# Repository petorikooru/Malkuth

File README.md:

# Malkuth

Idk, the name just comes up in my head (that malkuth from BA)

> [!CAUTION]
> For now, DO NOT USE the PCB Design unless you know what you are doing.
> There are quite silly (and tiny bit major) design flaws on there

> [!NOTE]  
> For now, the audio handling is a bit stuttery on some FLAC audio
> (especially on 24 bit one). I will make it a todo list for now

Basically it is a rewrite version of the previous project of mine [uta](https://github.com/petorikooru/uta)

I create this to fulfill my final project of Microcomputer class lmao.

## Dependencies

- TFT_eSPI + FT6236 + PNGdec
- arduino-audio-tools + libfoxenflac + libmp3helix + libaac + libwav
- SdFat

## Hardware Components

- ILI9488 Capacitive Touch Screen Display
- PCM5102a DAC
- MicroSD Card Module
- ESP32-S3 N16R8
- Kailh Choc v2 switch
- Other small components stuff

For now, 16 MB Storage size is needed to keep the font files (they take like 50% of the spaces 💀). I will make them .vlw files and store it inside SPIFFS or LittleFS (that is the task of future me though)

## Screenshot

<table>
  <tr>
    <td> </td>
    <td> </td>
    <td> </td>
  </tr> 
</table>

## TODO List

- Make the audio a task itself just like Display (The main trouble is that SdFat is not really thread safe)
- Actually handle audio cover image (jpg and png)
- More performance fixing stuff
- ~Actually handle UI correctly instead of reloading from scratch~ (Kinda done?)
- 3D Printable Case

## Far (not really) to the future TODO LIST

- Maybe split the processing to different chip so that the Display will be driven by RP2040 and the Audio (and perhaps even bluetooth functionality) will be driven by ESP32-S3 (or more powerful counterpart)
- Fix the PCB Design and implement actual charging functionality
- Add speaker (maybe will salvage from iphone speaker or something) and implement automatic audio switching
- RTC clock?
- Animation (i dont think it is powerful enough though)

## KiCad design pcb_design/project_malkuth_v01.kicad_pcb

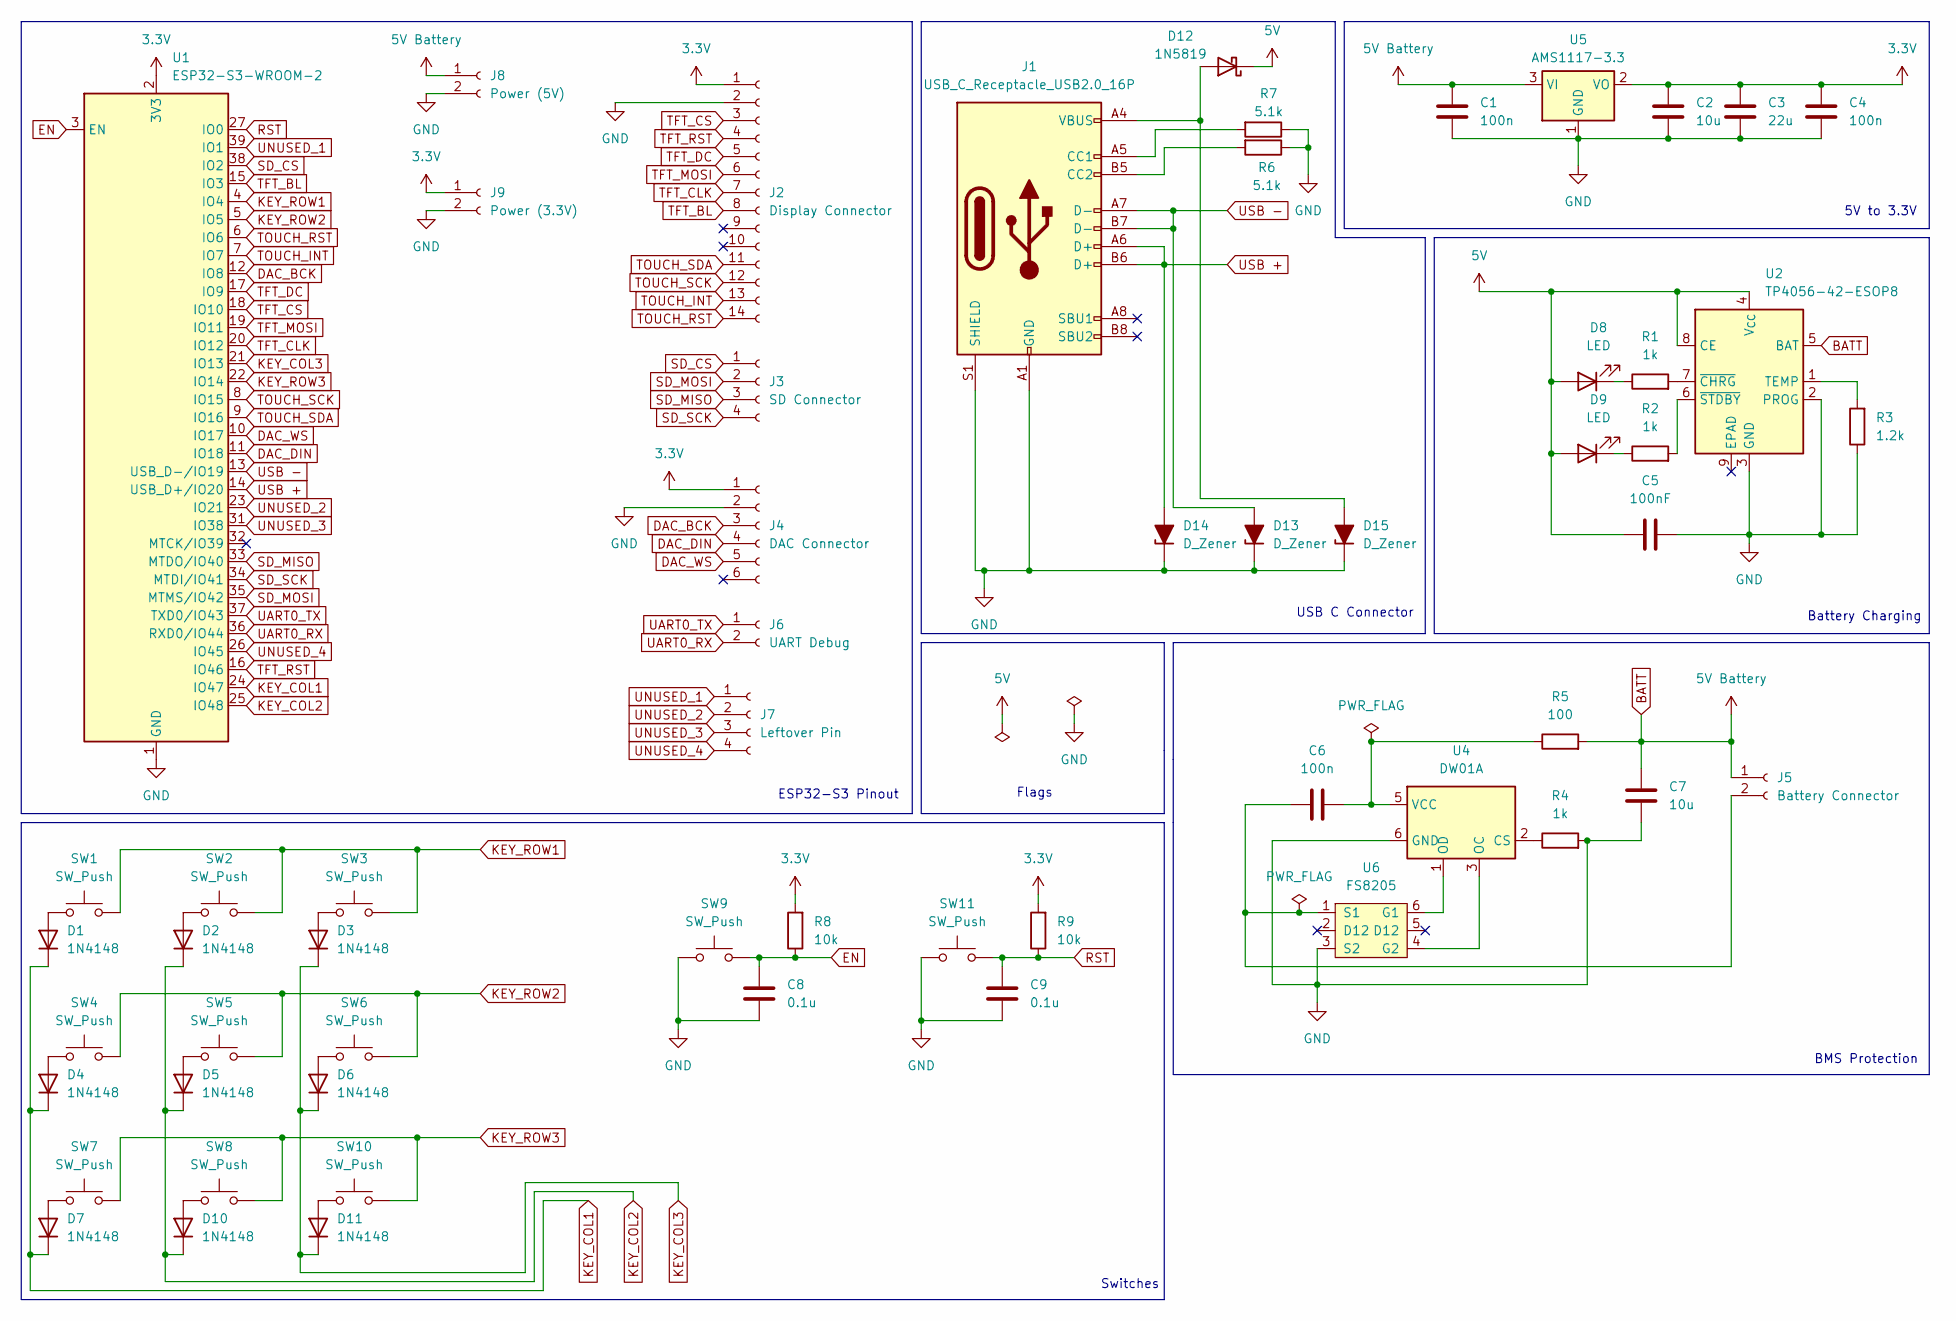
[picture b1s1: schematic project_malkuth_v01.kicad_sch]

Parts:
C1, C4, C6: 100n; C_0805_2012Metric
C2, C7: 10u; C_0805_2012Metric
C3: 22u; C_0805_2012Metric
C5: 100nF
C8, C9: 0.1u
D1, D2, D3, D4, D5, D6, D7, D10, D11: 1N4148; D_DO-35_SOD27_P7.62mm_Horizontal
D8, D9: LED; LED_0805_2012Metric
D12: 1N5819; D_DO-41_SOD81_P10.16mm_Horizontal
D13, D14, D15: D_Zener; Littelfuse_PolyZen-LS
J1: USB_C_Receptacle_USB2.0_16P; USB_C_Receptacle_GCT_USB4105-xx-A_16P_TopMnt_Horizontal
J2: Display Connector; PinSocket_1x14_P2.00mm_Vertical
J3: SD Connector; PinSocket_1x04_P2.00mm_Vertical
J4: DAC Connector; PinHeader_1x06_P2.00mm_Vertical
J5: Battery Connector; PinSocket_1x02_P2.54mm_Vertical
J6: UART Debug; PinSocket_1x02_P2.00mm_Vertical
J7: Leftover Pin; PinSocket_1x04_P2.00mm_Vertical
J8: Power (5V); PinSocket_1x02_P2.00mm_Vertical
J9: Power (3.3V); PinSocket_1x02_P2.00mm_Vertical
R1, R2, R4: 1k; R_0805_2012Metric
R3: 1.2k; R_0805_2012Metric
R5: 100; R_0805_2012Metric
R6, R7: 5.1k; R_0805_2012Metric
R8, R9: 10k; R_0805_2012Metric
SW1, SW2, SW3: SW_Push; SW_Hotswap_Kailh_Choc_V1V2
SW4, SW5, SW6, SW7, SW8, SW10: SW_Push; SW_Tactile_SPST_Angled_PTS645Vx39-2LFS
SW9, SW11: SW_Push; SW_PUSH_6mm
U1: ESP32-S3-WROOM-2
U2: TP4056-42-ESOP8; SOIC-8-1EP_3.9x4.9mm_P1.27mm_EP2.41x3.3mm_ThermalVias
U4: DW01A; SOT-23-6
U5: AMS1117-3.3; SOT-223-3_TabPin2
U6: FS8205; SOT-23-6; LCSC C32254

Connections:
3.3V: C2.1, C3.1, C4.1, J2.1, J4.1, J9.1, R8.2, R9.2, U1.2 (3V3), U5.2 (VO)
5V: C5.2, D8.2 (A), D9.2 (A), D12.1 (K), U2.4 (V_{CC}), U2.8 (CE)
BATT: C1.1, C7.1, J5.1, J8.1, R5.2, U2.5 (BAT), U5.3 (VI)
DAC_BCK: J4.3, U1.12 (IO8)
DAC_DIN: J4.4, U1.11 (IO18)
DAC_WS: J4.5, U1.10 (IO17)
EN: C8.1, R8.1, SW9.2, U1.3 (EN)
GND: C1.2, C2.2, C3.2, C4.2, C5.1, C7.2, C8.2, C9.2, D13.1 (K), D14.1 (K), D15.1 (K), J1.A1 (GND), J1.A12 (GND), J1.B1 (GND), J1.B12 (GND), J1.S1 (SHIELD), J2.2, J4.2, J8.2, J9.2, R3.1, R4.2, R6.1, R7.1, SW9.1, SW11.1, U1.1 (GND), U1.40 (GND), U1.41 (GND), U2.2 (PROG), U2.3 (GND), U4.6 (GND), U5.1 (GND), U6.3 (S2)
KEY_COL1: D1.1 (K), D4.1 (K), D7.1 (K), U1.24 (IO47)
KEY_COL2: D2.1 (K), D5.1 (K), D10.1 (K), U1.25 (IO48)
KEY_COL3: D3.1 (K), D6.1 (K), D11.1 (K), U1.21 (IO13)
KEY_ROW1: SW1.2, SW2.2, SW3.2, U1.4 (IO4)
KEY_ROW2: SW4.2, SW5.2, SW6.2, U1.5 (IO5)
KEY_ROW3: SW7.2, SW8.2, SW10.2, U1.22 (IO14)
unnamed: D1.2 (A), SW1.1
unnamed: D2.2 (A), SW2.1
unnamed: D3.2 (A), SW3.1
unnamed: D4.2 (A), SW4.1
unnamed: D5.2 (A), SW5.1
unnamed: D6.2 (A), SW6.1
unnamed: D7.2 (A), SW7.1
unnamed: D8.1 (K), R1.1
unnamed: D9.1 (K), R2.1
unnamed: D10.2 (A), SW8.1
unnamed: D11.2 (A), SW10.1
unnamed: D12.2 (A), D15.2 (A), J1.A4 (VBUS), J1.A9 (VBUS), J1.B4 (VBUS), J1.B9 (VBUS)
unnamed: J1.A5 (CC1), R7.2
unnamed: J1.B5 (CC2), R6.2
unnamed: C6.1, J5.2, U6.1 (S1)
unnamed: R3.2, U2.1 (TEMP)
unnamed: R1.2, U2.7 (~CHRG)
unnamed: R2.2, U2.6 (~STDBY)
unnamed: R4.1, U4.2 (CS)
unnamed: U4.3 (OC), U6.4 (G2)
unnamed: U4.1 (OD), U6.6 (G1)
unnamed: C6.2, R5.1, U4.5 (VCC)
RST: C9.1, R9.1, SW11.2, U1.27 (IO0)
SD_CS: J3.1, U1.38 (IO2)
SD_MISO: J3.3, U1.33 (MTDO/IO40)
SD_MOSI: J3.2, U1.35 (MTMS/IO42)
SD_SCK: J3.4, U1.34 (MTDI/IO41)
TFT_BL: J2.8, U1.15 (IO3)
TFT_CLK: J2.7, U1.20 (IO12)
TFT_CS: J2.3, U1.18 (IO10)
TFT_DC: J2.5, U1.17 (IO9)
TFT_MOSI: J2.6, U1.19 (IO11)
TFT_RST: J2.4, U1.16 (IO46)
TOUCH_INT: J2.13, U1.7 (IO7)
TOUCH_RST: J2.14, U1.6 (IO6)
TOUCH_SCK: J2.12, U1.8 (IO15)
TOUCH_SDA: J2.11, U1.9 (IO16)
UART0_RX: J6.2, U1.36 (RXD0/IO44)
UART0_TX: J6.1, U1.37 (TXD0/IO43)
UNUSED_1: J7.1, U1.39 (IO1)
UNUSED_2: J7.2, U1.23 (IO21)
UNUSED_3: J7.3, U1.31 (IO38)
UNUSED_4: J7.4, U1.26 (IO45)
USB +: D14.2 (A), J1.A6 (D+), J1.B6 (D+), U1.14 (USB_D+/IO20)
USB -: D13.2 (A), J1.A7 (D-), J1.B7 (D-), U1.13 (USB_D-/IO19)

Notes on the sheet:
5V to 3.3V
Flags
BMS Protection
Switches
ESP32-S3 Pinout
Battery Charging
USB C Connector

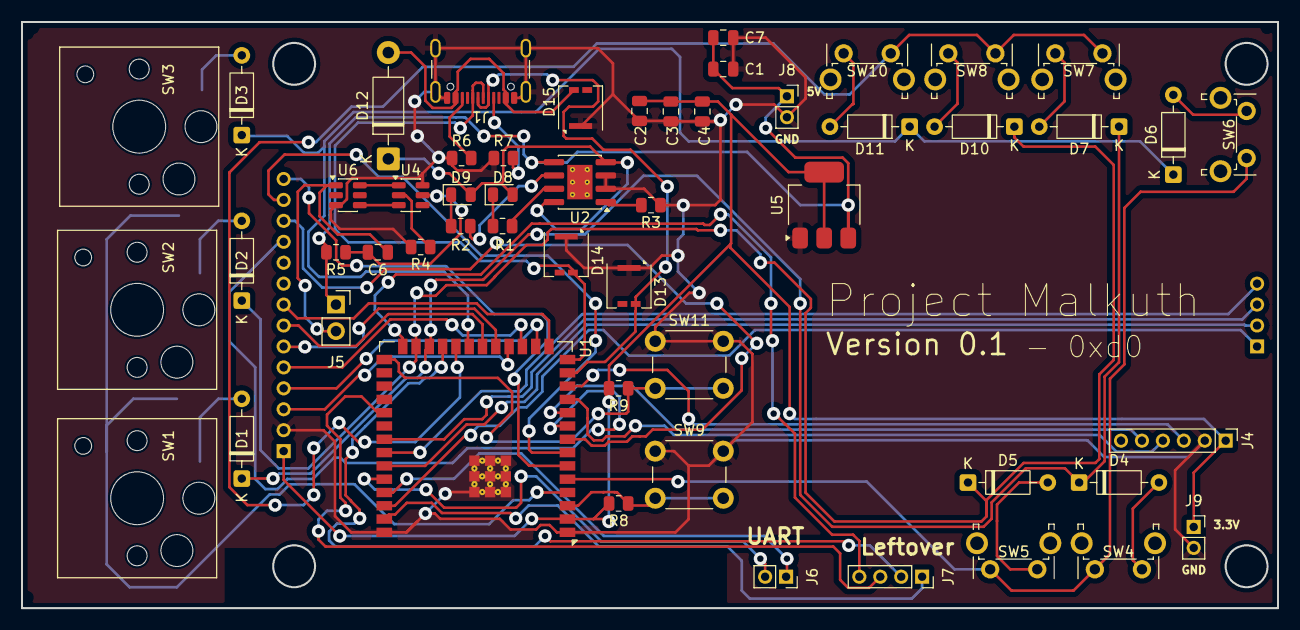
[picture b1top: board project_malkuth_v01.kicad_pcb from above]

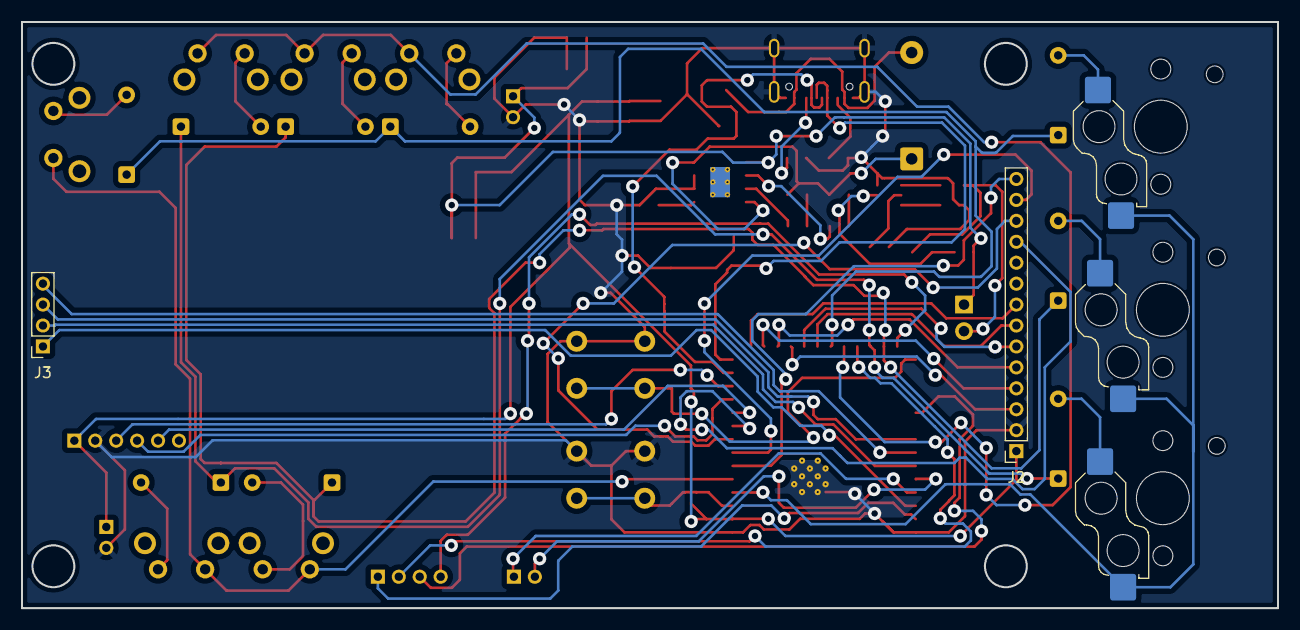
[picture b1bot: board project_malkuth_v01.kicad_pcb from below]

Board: 2 copper layers, 120.0 x 56.0 mm, 55 parts (2 on the bottom side), 59 nets.

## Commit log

2026-01-02 HUGE Update basically
2026-01-02 Cleaning up some files
2026-01-02 Fix typo
2026-01-02 Fancify Readme
2026-01-02 fix typo on dac name
2026-01-02 Create LICENSE
2026-01-04 Code cleanup
2026-01-07 UI Rendering is now localised + Rework some delay functions so that they are now non-blocking
2026-01-11 Quite an overhaul on "files" page + You can now press the audio file to actually play it instead of needing to press the "select" button now
2026-01-11 Updated the images
